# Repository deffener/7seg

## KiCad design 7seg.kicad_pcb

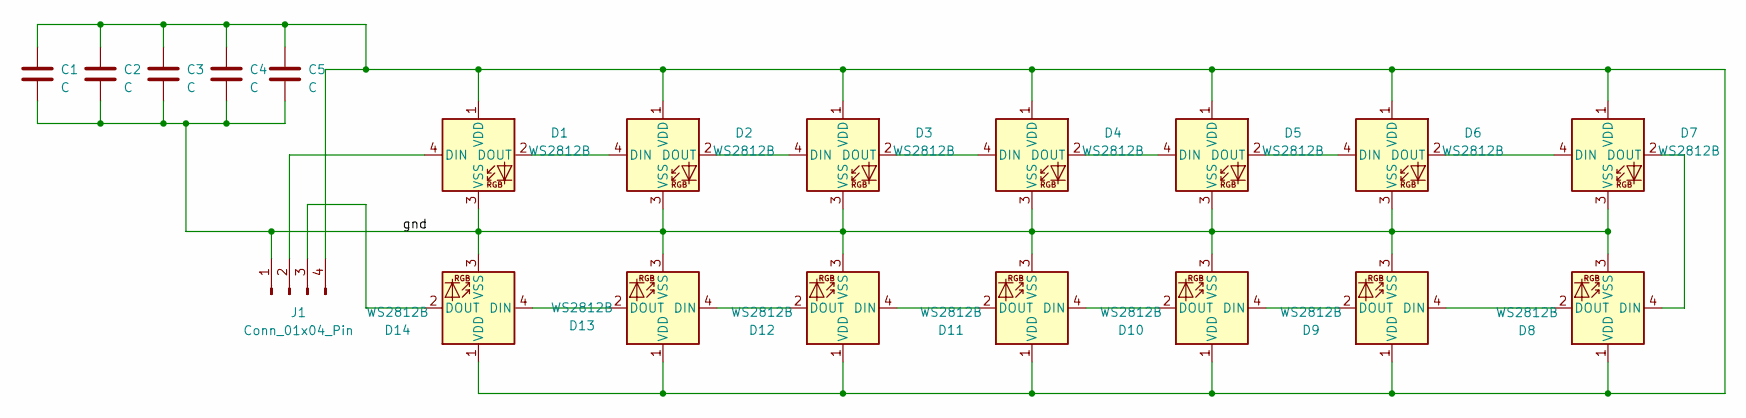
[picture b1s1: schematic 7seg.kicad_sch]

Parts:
C1, C2, C3, C4, C5: C; C_1210_3225Metric_Pad1.33x2.70mm_HandSolder
D1, D2, D3, D4, D5, D6, D7, D8, D9, D10, D11, D12, D13, D14: WS2812B; LED_WS2812B_PLCC4_5.0x5.0mm_P3.2mm
J1: Conn_01x04_Pin; JST_XH_S4B-XH-A-1_1x04_P2.50mm_Horizontal

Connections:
/gnd: C1.2, C2.2, C3.2, C4.2, C5.2, D1.3 (VSS), D2.3 (VSS), D3.3 (VSS), D4.3 (VSS), D5.3 (VSS), D6.3 (VSS), D7.3 (VSS), D8.3 (VSS), D9.3 (VSS), D10.3 (VSS), D11.3 (VSS), D12.3 (VSS), D13.3 (VSS), D14.3 (VSS), J1.1
unnamed: D1.4 (DIN), J1.2
unnamed: D1.2 (DOUT), D2.4 (DIN)
unnamed: C1.1, C2.1, C3.1, C4.1, C5.1, D1.1 (VDD), D2.1 (VDD), D3.1 (VDD), D4.1 (VDD), D5.1 (VDD), D6.1 (VDD), D7.1 (VDD), D8.1 (VDD), D9.1 (VDD), D10.1 (VDD), D11.1 (VDD), D12.1 (VDD), D13.1 (VDD), D14.1 (VDD), J1.4
unnamed: D2.2 (DOUT), D3.4 (DIN)
unnamed: D3.2 (DOUT), D4.4 (DIN)
unnamed: D4.2 (DOUT), D5.4 (DIN)
unnamed: D5.2 (DOUT), D6.4 (DIN)
unnamed: D6.2 (DOUT), D7.4 (DIN)
unnamed: D7.2 (DOUT), D8.4 (DIN)
unnamed: D8.2 (DOUT), D9.4 (DIN)
unnamed: D9.2 (DOUT), D10.4 (DIN)
unnamed: D10.2 (DOUT), D11.4 (DIN)
unnamed: D11.2 (DOUT), D12.4 (DIN)
unnamed: D12.2 (DOUT), D13.4 (DIN)
unnamed: D13.2 (DOUT), D14.4 (DIN)
unnamed: D14.2 (DOUT), J1.3

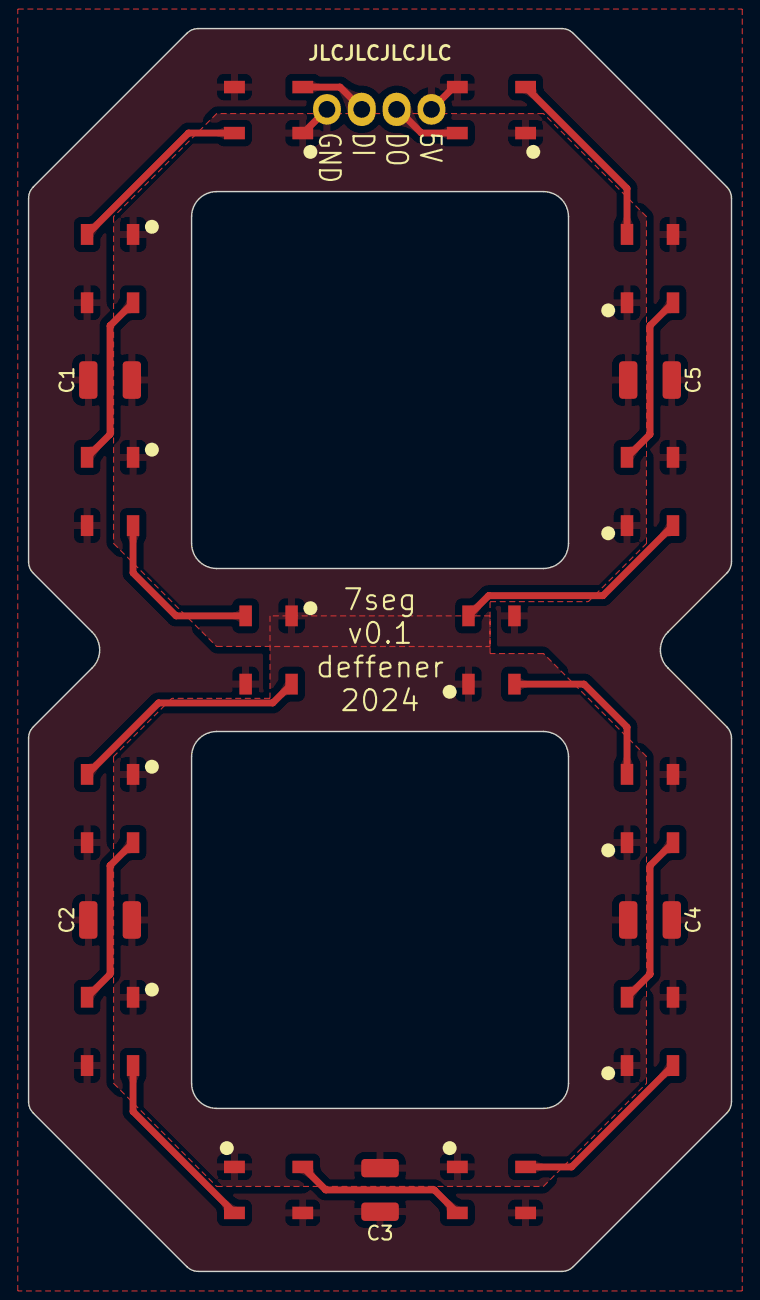
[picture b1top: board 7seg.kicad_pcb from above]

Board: 2 copper layers, 50.4 x 89.2 mm, 20 parts (1 on the bottom side), 17 nets.

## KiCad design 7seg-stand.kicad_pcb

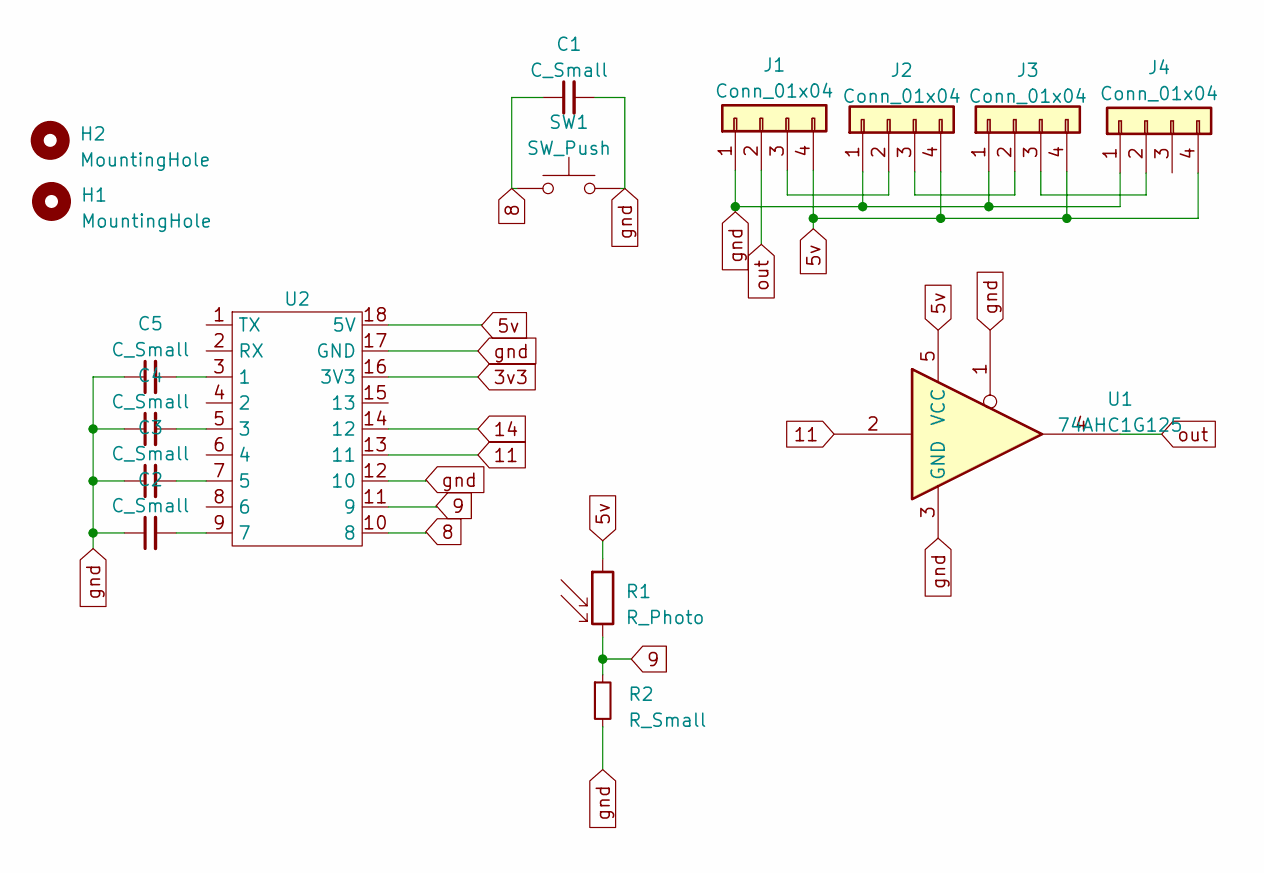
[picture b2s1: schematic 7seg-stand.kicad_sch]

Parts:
C1, C2, C3, C4, C5: C_Small; C_0603_1608Metric_Pad1.08x0.95mm_HandSolder
H1, H2: MountingHole; MountingHole_3.2mm_M3
J1, J2, J3, J4: Conn_01x04; PinSocket_1x04_P2.54mm_Vertical
R1: R_Photo; R_LDR_5.1x4.3mm_P3.4mm_Vertical
R2: R_Small; R_0603_1608Metric_Pad0.98x0.95mm_HandSolder
SW1: SW_Push; SW_Push_1P1T_XKB_TS-1187A
U1: 74AHC1G125; SOT-353_SC-70-5_Handsoldering
U2: ESP32-S3_supermini

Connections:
3v3: U2.16 (3V3)
5v: J1.4, J2.4, J3.4, J4.4, R1.1, U1.5 (VCC), U2.18 (5V)
8: C1.1, SW1.1, U2.10 (8)
9: R1.2, R2.1, U2.11 (9)
11: U1.2, U2.13 (11)
14: U2.14 (12)
unnamed: J1.3, J2.2
unnamed: J2.3, J3.2
unnamed: J3.3, J4.2
unnamed: C5.2, U2.3 (1)
unnamed: C4.2, U2.5 (3)
unnamed: C3.2, U2.7 (5)
unnamed: C2.2, U2.9 (7)
gnd: C1.2, C2.1, C3.1, C4.1, C5.1, J1.1, J2.1, J3.1, J4.1, R2.2, SW1.2, U1.1, U1.3 (GND), U2.12 (10), U2.17 (GND)
out: J1.2, U1.4

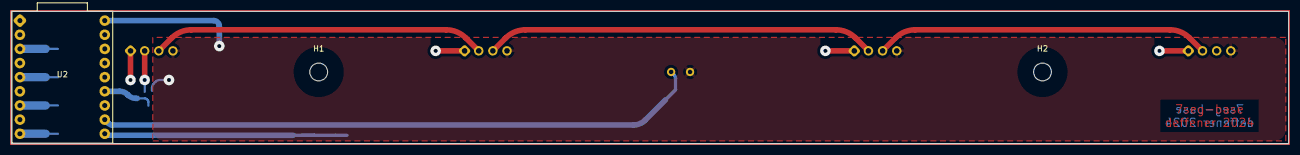
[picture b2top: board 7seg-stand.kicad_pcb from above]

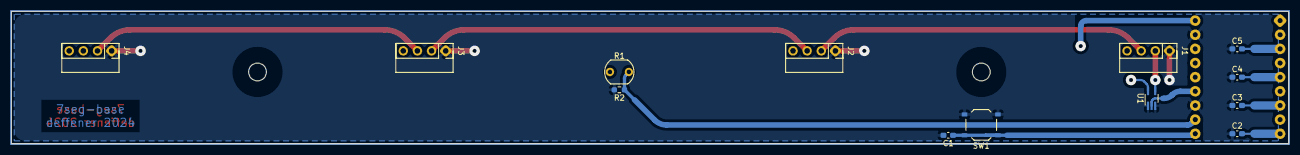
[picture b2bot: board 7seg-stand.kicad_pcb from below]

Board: 2 copper layers, 229.4 x 23.7 mm, 16 parts (13 on the bottom side), 13 nets.

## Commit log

2025-03-02 revikka 1
